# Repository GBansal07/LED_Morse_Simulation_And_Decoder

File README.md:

# LED_Morse_Simulation_And_Decoder
I created an LED Morse Decoder for my UWindsor Mars Rover Team that competes in the Canadian International Rover Challenge. I also created my own simulation with a few randomized parameters using an LED. The Morse Decoder program is in the same file and works normally because I use millis() for non-blocking functionality.

Now here are my thoughts and design process for this project:
The first thing I did was learn a sufficient amount of Morse code to be able to program logic into an Arduino, converting LED timing intervals into numbers and letters. After some research about Morse, I constructed a simulation to randomly generate an alphanumeric code (fancy word for a code that only consists of the English letters and numbers), convert it to Morse (dots and dashes), then to timings, and blink an LED I wired to an Arduino NANO through a breadboard. I laid this out in a clear and concise way, but actually doing it took lots of time. Coming into this project, I knew a bit about wiring electrical components, and I was very familiar with using Arduinos for hobby projects, but I was not comfortable with programming in the Arduino IDE/C++ enough for such a programming-dependent project. So, the first thing I did was get to learning through the latest free version of Claude. I learned a lot about arrays, like using a char array for letters/numbers and char* for the Morse code that corresponds to each, and they have the same index in each array, so it was easy to communicate with other functions in the code. I completely randomized as many parameters as I could as well, just so my decoder could be prepared for different codes at competition. The code was randomly picked 8-12 characters and sometimes included 1 or 2 spaces, and as for the Morse unit of time, the CIRC website released that it was 66 ms, but before I would generate a random number between 200-600ms. From this, I generated the code, and all I had to do was convert random letters/numbers to Morse code, then use the Morse unit to calculate on and off timings that would be stored in two other arrays. To finish off the simulation part of the project, I took the on/off timings that were stored and used the millis() function on the LED to tell it how long it needed to be on or off by just flipping back and forth between the on and off timing arrays. I learned quite a bit about millis(), like that it’s more preferred to use instead of delay() because delay() stops the entire program, while millis() keeps it running, hence why millis() is referred to as non-blocking. The main reason why I used millis() is that I was planning on using the same microcontroller to read the LED Morse code, so I couldn’t stop the code whenever I wanted to blink the LED, because I needed to time the on and off times that my decoder would read from the LED to get information and translate the code.
	
Next, I developed a decoder using a light-dependent resistor (LDR) to detect the light from the LED. I would get the delta of the times from calling the millis() function at the start and end, both when the LED is on and off, then store the timings in an array. Then, from the array, I would use the given 66ms Morse unit with some tolerance to convert the on and off timings into Morse, then from the Morse, I would go back and forth between the Morse arrays to construct the alphanumeric code.

Prototyping obviously didn’t go smoothly; I made so many mistakes. One of my most memorable mistakes was that I, without much thought, wired an LDR with an analog pin on one end and the other end going through ground. I quickly found that I was reading nothing when I would test my values on the Serial Monitor. This mistake taught me a lot about LDRs and why they are wired the way they are for an application where they are used as a sensor. An LDR is simply a resistor, so wiring it in a loop with the Arduino gives no information, since the analog pin that it’s connected to reads changes in voltage. With the resistor in a closed loop, there’s no variable voltage, so I got no meaningful information from the sensor. With this issue, I searched for how to wire an LDR with an Arduino and found that I had to create a voltage divider. The way it works is: I put the analog pin node, connected to the Arduino, between the static resistor and the light-dependent one and measure the change in voltage between them. This gave me a number between 0 and 1023 that I could use as a “light level” to help me identify when the LED is on or off. As for programming, I would write code and explain my logic function-by-function to Claude and have it teach me where my programming logic is flawed. With the AI, I would work with it by writing my logic in the prompt rather than just letting it do its own thing, and I can’t understand and bugfix. This process takes longer, but I got to learn lots about concepts like the different ways to use the millis() function and how to work with random-size arrays with null terminators.

The physical circuit stayed intentionally simple: one photoresistor, one static resistor forming a voltage divider, and an LED; no op-amps, comparators, or dedicated debouncing ICs. All the noise handling lives in software, which kept the bill of materials to three components and made the whole thing easy to reproduce and cheap to build. 

 After prototyping, I designed a PCB in KiCad from scratch by learning the steps and UI from YouTube tutorials, then drawing out the circuit I designed with the prototype. After designing, I sent my Gerber files to the IDEA Lab at UWindsor to get my PCBs printed, and then I soldered my electronics onto them.

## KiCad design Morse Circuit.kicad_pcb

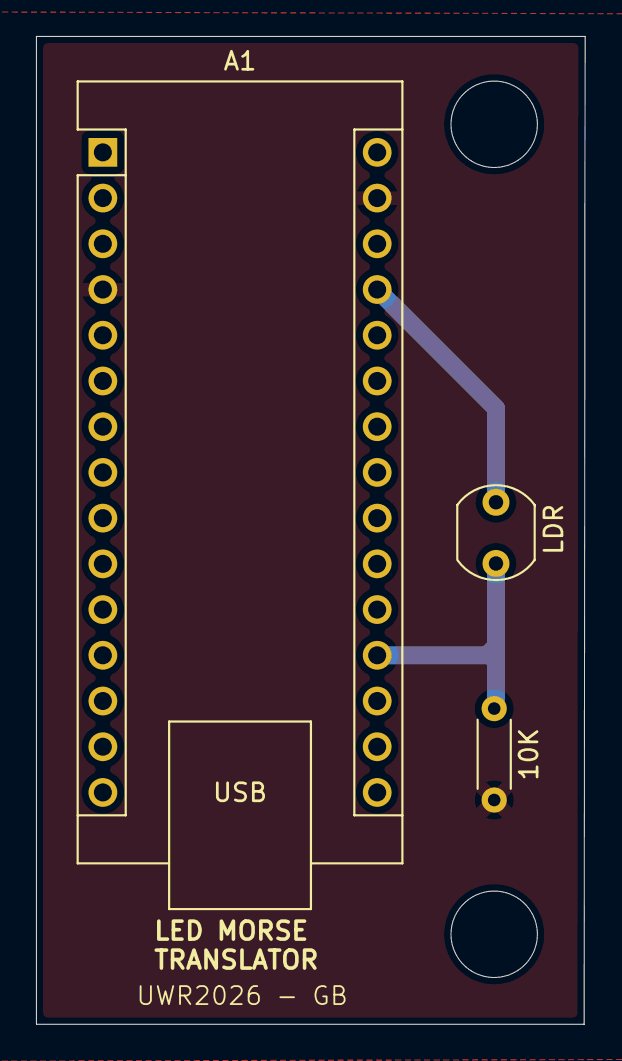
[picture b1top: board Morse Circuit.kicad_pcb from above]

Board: 4 copper layers, 30.5 x 54.9 mm, 3 parts (0 on the bottom side), 3 nets.

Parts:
10K: R; R_Axial_DIN0204_L3.6mm_D1.6mm_P5.08mm_Horizontal
A1: Arduino_Nano_v3.x; Arduino_Nano
LDR: LDR07; R_LDR_5.1x4.3mm_P3.4mm_Vertical

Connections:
+5V: A1.27 (+5V), LDR.1
GND: 10K.2, A1.4 (GND), A1.29 (GND)
unnamed: 10K.1, A1.19 (A0), LDR.2
